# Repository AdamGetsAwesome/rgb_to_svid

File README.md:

# rgb_to_svid
Eagle project for a circuit to convert RGB signals from old PCs (Atari/Amiga) to s-video

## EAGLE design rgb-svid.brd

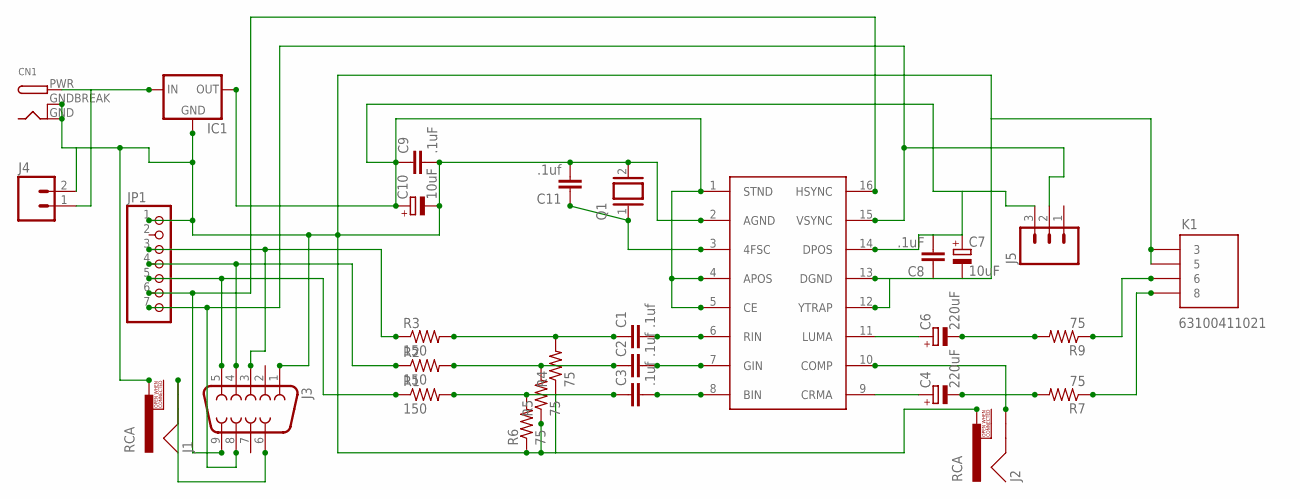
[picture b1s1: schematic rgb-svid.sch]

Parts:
C1, C2, C3, C11: .1uf; C2.5-2
C4, C6: 220uF; E2-5
C7, C10: 10uF; E2-5
C8, C9: .1uF; C2.5-2
CN1: DCBARRELPTH; DCJACK_2MM_PTH
IC1: 78XXL
J1, J2: RCA
J3: DB9FEMALE; DB9
J4: M02LOCK; 1X02_LOCK
J5: M03PTH; 1X03
JP1: PINHD-1X7; 1X07
K1: 63100411021
Q1: XTAL/S; QS
R1, R2, R3: 150; 0207/12
R4, R5, R6, R7, R9: 75; 0207/12
U$1: AD725; SO16W

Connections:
AUDIO_OUT: J1.SHELL, J3.6
C_VID_OUT: J2.SHELL, U$1.10 (COMP)
GND: C7.-, C8.1, C9.2, C10.-, C11.2, CN1.GND, CN1.GNDBREAK, IC1.GND, J1.PIN, J2.PIN, J3.1, J4.2, JP1.1, K1.3, K1.5, Q1.2, R4.1, R5.1, R6.1, U$1.2 (AGND), U$1.12 (YTRAP), U$1.13 (DGND)
unnamed: C1.1, R3.2, R4.2
unnamed: C2.1, R2.2, R5.2
unnamed: C7.+, C8.2, C9.1, C10.+, IC1.OUT, J5.3, U$1.1 (STND), U$1.4 (APOS), U$1.5 (CE), U$1.14 (DPOS)
unnamed: C3.1, R1.2, R6.2
unnamed: C4.-, R7.2
unnamed: J3.9, JP1.6, U$1.16 (HSYNC)
unnamed: C6.-, R9.2
unnamed: C4.+, U$1.9 (CRMA)
unnamed: K1.6, R9.1
unnamed: CN1.PWR, IC1.IN, J4.1
unnamed: K1.8, R7.1
unnamed: C11.1, Q1.1, U$1.3 (4FSC)
unnamed: C6.+, U$1.11 (LUMA)
unnamed: J3.4, JP1.4, R2.1
unnamed: J3.5, JP1.5, R1.1
unnamed: J3.8, J5.2, JP1.7, U$1.15 (VSYNC)
unnamed: C3.2, U$1.8 (BIN)
unnamed: C2.2, U$1.7 (GIN)
unnamed: C1.2, U$1.6 (RIN)
unnamed: J3.3, JP1.3, R3.1

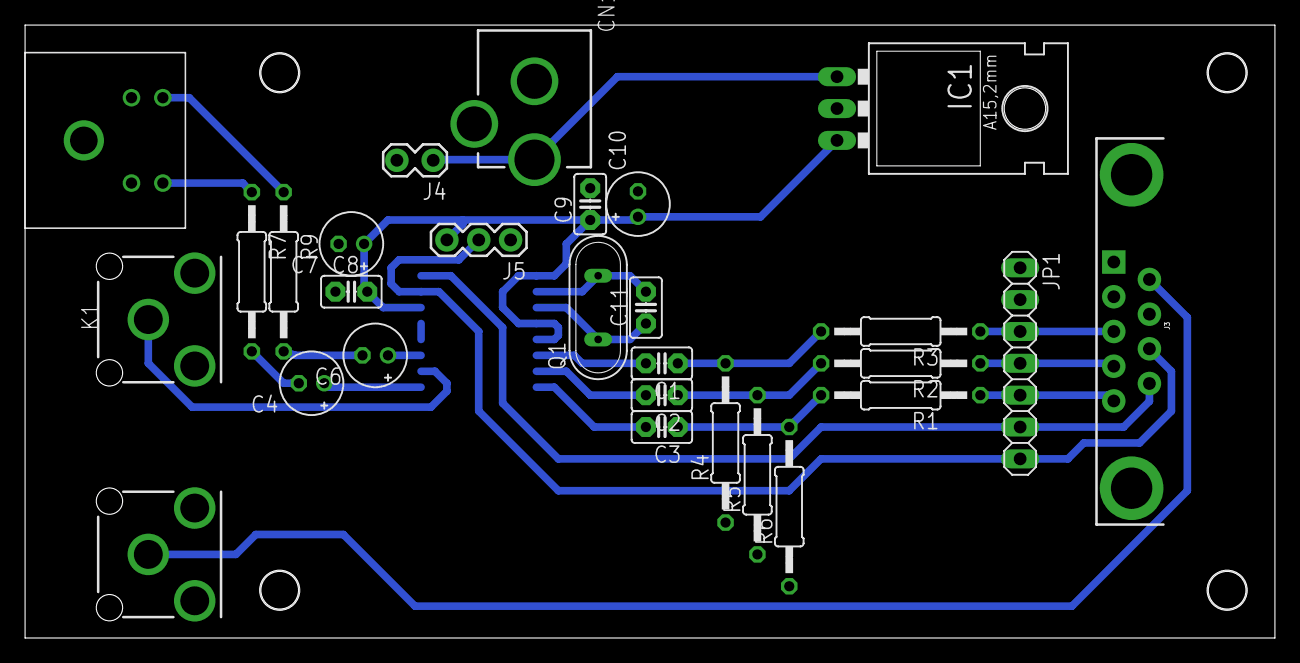
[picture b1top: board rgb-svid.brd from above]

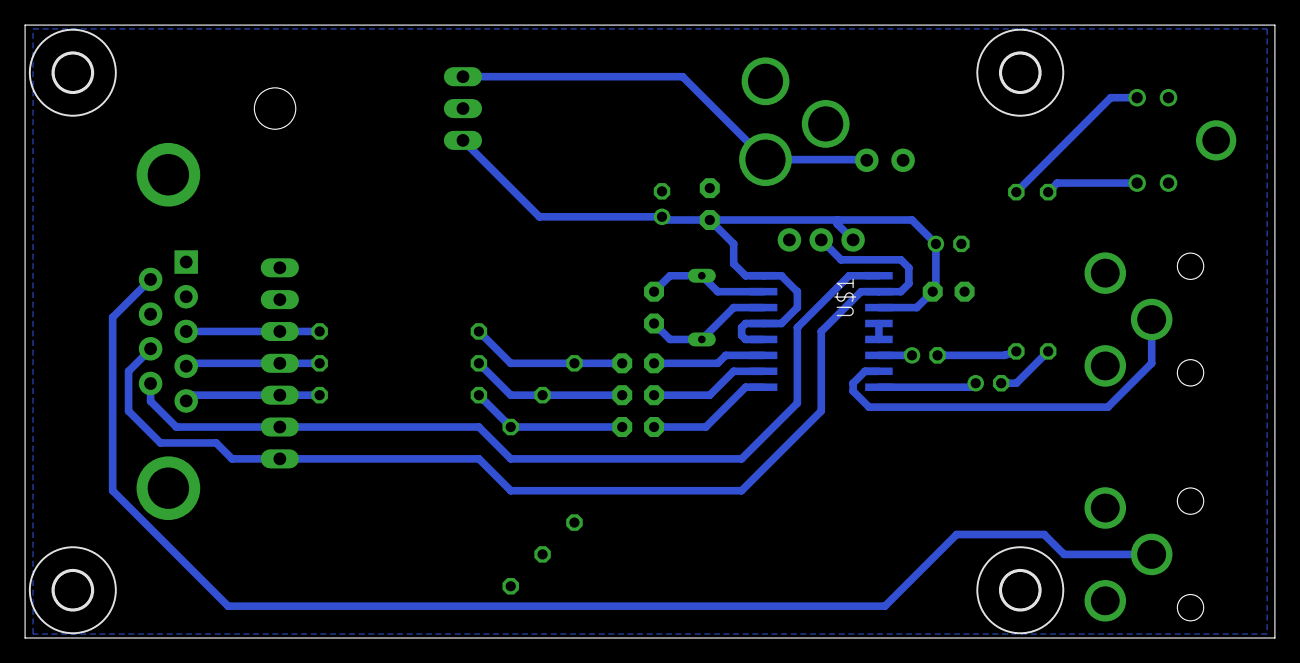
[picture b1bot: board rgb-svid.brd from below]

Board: 1 copper layer, 99.7 x 48.9 mm, 33 parts (5 on the bottom side), 23 nets.

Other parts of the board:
U$2, U$3, U$4, U$5: 3,0

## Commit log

2018-04-25 Adding project to github
2018-04-25 Minor change on GND polygon.

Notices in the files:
parts and their libraries:
Wuerth_Elektronik_eiCan_Communication_Co: Copyright: Würth Elektronik
SparkFun-Connectors: Licensing: Creative Commons ShareAlike 4.0 International - https://creativecommons.org/licenses/by-sa/4.0
